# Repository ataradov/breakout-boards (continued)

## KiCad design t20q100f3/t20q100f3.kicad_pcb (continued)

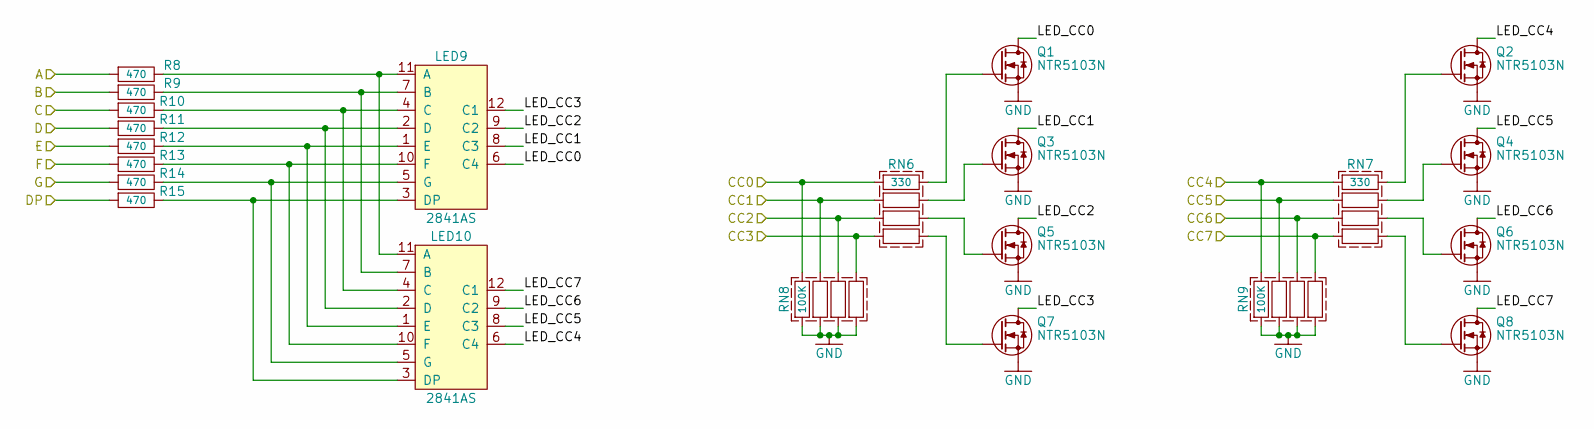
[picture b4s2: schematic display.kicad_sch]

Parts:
LED9, LED10: 2841AS
Q1, Q2, Q3, Q4, Q5, Q6, Q7, Q8: NTR5103N; SOT-23
R8, R9, R10, R11, R12, R13, R14, R15: 470; 0603
RN6, RN7: 330; 0603x4
RN8, RN9: 100K; 0603x4

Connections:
/Display/LED_CC0: LED9.6 (C4), Q1.3 (D)
/Display/LED_CC1: LED9.8 (C3), Q3.3 (D)
/Display/LED_CC2: LED9.9 (C2), Q5.3 (D)
/Display/LED_CC3: LED9.12 (C1), Q7.3 (D)
/Display/LED_CC4: LED10.6 (C4), Q2.3 (D)
/Display/LED_CC5: LED10.8 (C3), Q4.3 (D)
/Display/LED_CC6: LED10.9 (C2), Q6.3 (D)
/Display/LED_CC7: LED10.12 (C1), Q8.3 (D)
/LED_A: R8.1; also elsewhere on the board
/LED_B: R9.1; also elsewhere on the board
/LED_C: R10.1; also elsewhere on the board
/LED_CC0: RN6.1, RN8.8; also elsewhere on the board
/LED_CC1: RN6.2, RN8.7; also elsewhere on the board
/LED_CC2: RN6.3, RN8.6; also elsewhere on the board
/LED_CC3: RN6.4, RN8.5; also elsewhere on the board
/LED_CC4: RN7.1, RN9.8; also elsewhere on the board
/LED_CC5: RN7.2, RN9.7; also elsewhere on the board
/LED_CC6: RN7.3, RN9.6; also elsewhere on the board
/LED_CC7: RN7.4, RN9.5; also elsewhere on the board
/LED_D: R11.1; also elsewhere on the board
/LED_DP: R15.1; also elsewhere on the board
/LED_E: R12.1; also elsewhere on the board
/LED_F: R13.1; also elsewhere on the board
/LED_G: R14.1; also elsewhere on the board
GND: Q1.2 (S), Q2.2 (S), Q3.2 (S), Q4.2 (S), Q5.2 (S), Q6.2 (S), Q7.2 (S), Q8.2 (S), RN8.1, RN8.2, RN8.3, RN8.4, RN9.1, RN9.2, RN9.3, RN9.4; also elsewhere on the board
unnamed: LED9.11 (A), LED10.11 (A), R8.2
unnamed: LED9.7 (B), LED10.7 (B), R9.2
unnamed: LED9.4 (C), LED10.4 (C), R10.2
unnamed: LED9.2 (D), LED10.2 (D), R11.2
unnamed: LED9.3 (DP), LED10.3 (DP), R15.2
unnamed: LED9.1 (E), LED10.1 (E), R12.2
unnamed: LED9.10 (F), LED10.10 (F), R13.2
unnamed: LED9.5 (G), LED10.5 (G), R14.2
unnamed: Q1.1 (G), RN6.8
unnamed: Q2.1 (G), RN7.8
unnamed: Q3.1 (G), RN6.7
unnamed: Q4.1 (G), RN7.7
unnamed: Q5.1 (G), RN6.6
unnamed: Q6.1 (G), RN7.6
unnamed: Q7.1 (G), RN6.5
unnamed: Q8.1 (G), RN7.5

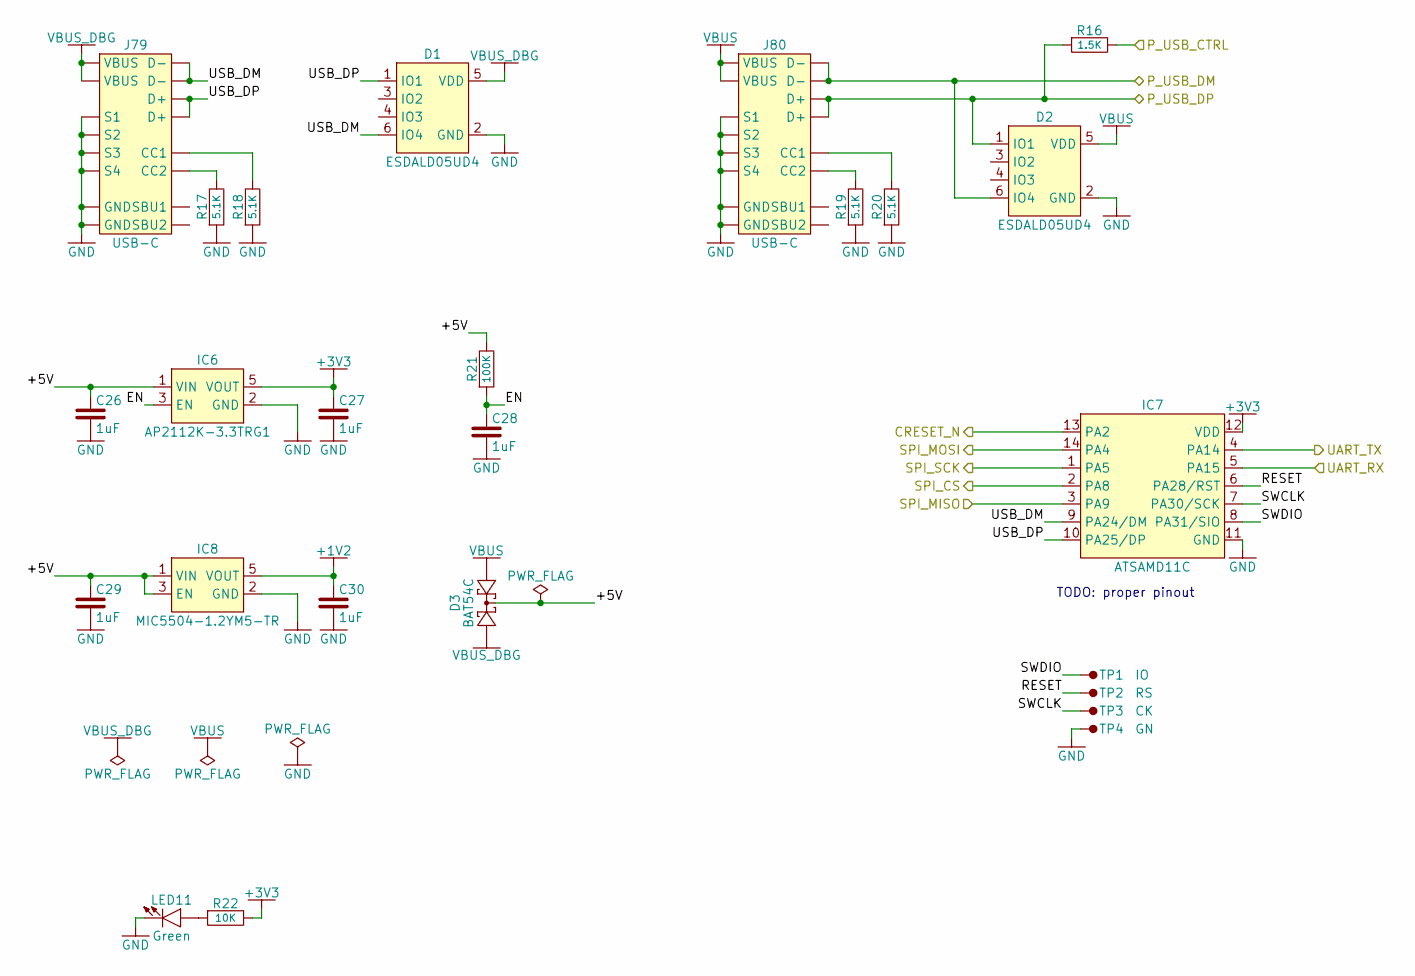
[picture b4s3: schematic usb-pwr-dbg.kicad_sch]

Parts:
C26, C27, C28, C29, C30: 1uF; 0603
D1, D2: ESDALD05UD4; SOT-23-6
D3: BAT54C; SOT-23
IC6: AP2112K-3.3TRG1; SOT-23-5
IC7: ATSAMD11C; SOIC-14
IC8: MIC5504-1.2YM5-TR; SOT-23-5
J79, J80: USB-C
LED11: Green; 0603_LED
R16: 1.5K; 0603
R17, R18, R19, R20: 5.1K; 0603
R21: 100K; 0603
R22: 10K; 0603
TP1: IO; TestPoint-1.27mm-SMD
TP2: RS; TestPoint-1.27mm-SMD
TP3: CK; TestPoint-1.27mm-SMD
TP4: GN; TestPoint-1.27mm-SMD

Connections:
+1V2: C30.2, IC8.5 (VOUT); also elsewhere on the board
+3V3: C27.2, IC6.5 (VOUT), IC7.12 (VDD), R22.2; also elsewhere on the board
/CRESET_N: IC7.13 (PA2); also elsewhere on the board
/P_USB_CTRL: R16.2; also elsewhere on the board
/P_USB_DM: D2.6 (IO4), J80.D-1 (D-), J80.D-2 (D-); also elsewhere on the board
/P_USB_DP: D2.1 (IO1), J80.D+1 (D+), J80.D+2 (D+), R16.1; also elsewhere on the board
/SPI_CS: IC7.2 (PA8); also elsewhere on the board
/SPI_MISO: IC7.3 (PA9); also elsewhere on the board
/SPI_MOSI: IC7.14 (PA4); also elsewhere on the board
/SPI_SCK: IC7.1 (PA5); also elsewhere on the board
/UART_RX: IC7.5 (PA15); also elsewhere on the board
/UART_TX: IC7.4 (PA14); also elsewhere on the board
/USB-Power-Debugger/+5V: C26.2, C29.2, D3.3, IC6.1 (VIN), IC8.1 (VIN), IC8.3 (EN), R21.2
/USB-Power-Debugger/EN: C28.2, IC6.3 (EN), R21.1
/USB-Power-Debugger/RESET: IC7.6 (PA28/RST), TP2.1
/USB-Power-Debugger/SWCLK: IC7.7 (PA30/SCK), TP3.1
/USB-Power-Debugger/SWDIO: IC7.8 (PA31/SIO), TP1.1
/USB-Power-Debugger/USB_DM: D1.6 (IO4), IC7.9 (PA24/DM), J79.D-1 (D-), J79.D-2 (D-)
/USB-Power-Debugger/USB_DP: D1.1 (IO1), IC7.10 (PA25/DP), J79.D+1 (D+), J79.D+2 (D+)
GND: C26.1, C27.1, C28.1, C29.1, C30.1, D1.2 (GND), D2.2 (GND), IC6.2 (GND), IC7.11 (GND), IC8.2 (GND), J79.GND1 (GND), J79.GND2 (GND), J79.S1, J79.S2, J79.S3, J79.S4, J80.GND1 (GND), J80.GND2 (GND), J80.S1, J80.S2, J80.S3, J80.S4, LED11.2 (K), R17.1, R18.1, R19.1, R20.1, TP4.1; also elsewhere on the board
unnamed: J79.CC1, R18.2
unnamed: J79.CC2, R17.2
unnamed: J80.CC1, R20.2
unnamed: J80.CC2, R19.2
unnamed: LED11.1 (A), R22.1
VBUS: D2.5 (VDD), D3.2, J80.VBUS1 (VBUS), J80.VBUS2 (VBUS)
VBUS_DBG: D1.5 (VDD), D3.1, J79.VBUS1 (VBUS), J79.VBUS2 (VBUS)

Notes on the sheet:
TODO: proper pinout

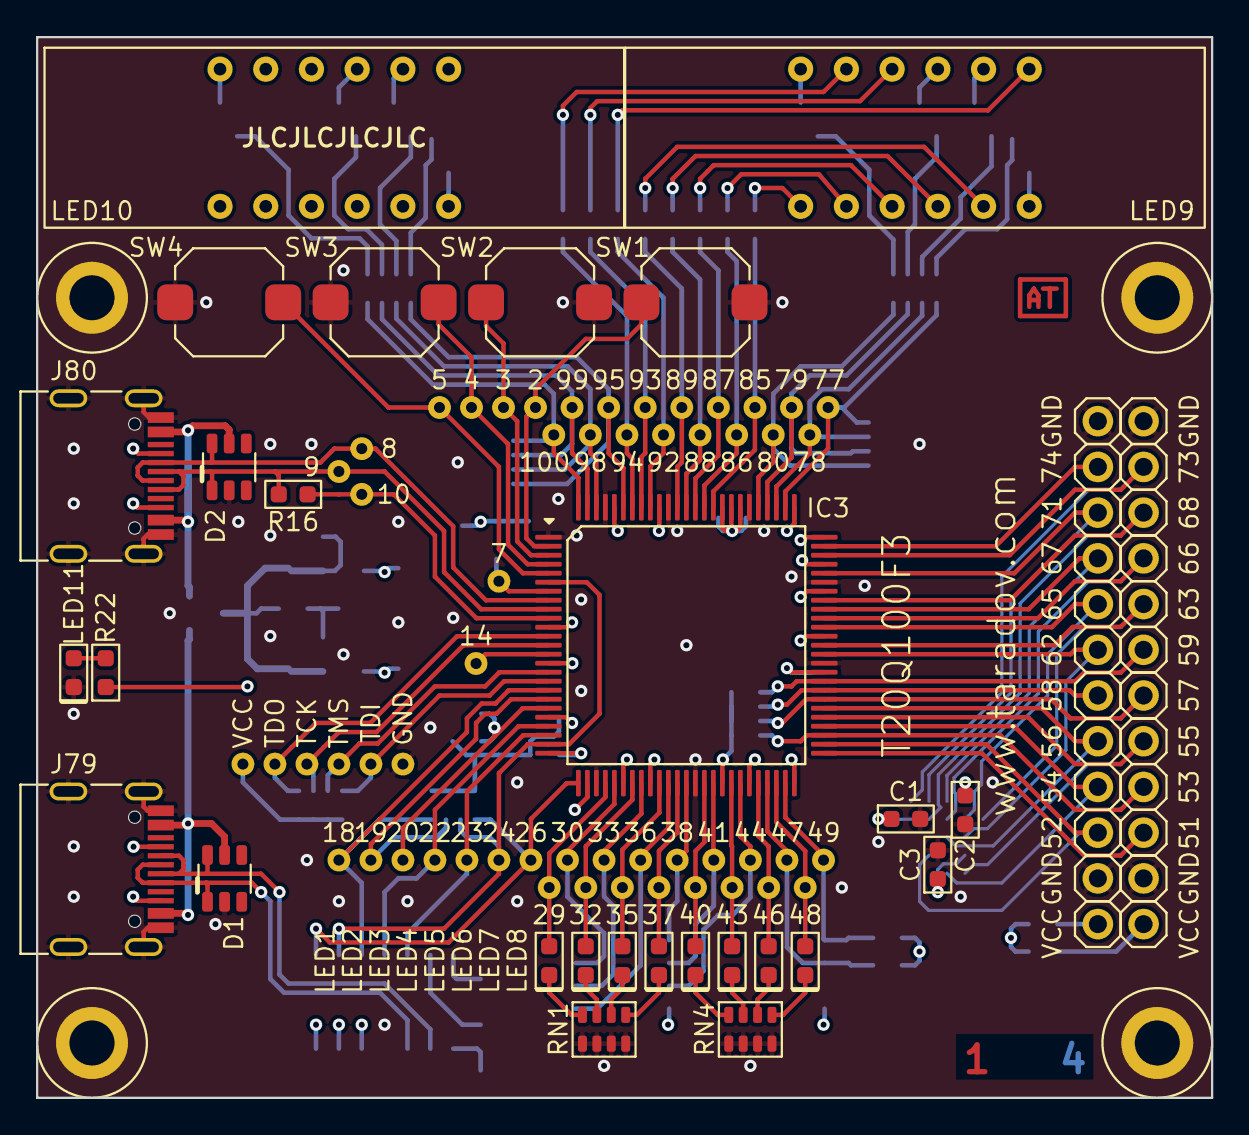
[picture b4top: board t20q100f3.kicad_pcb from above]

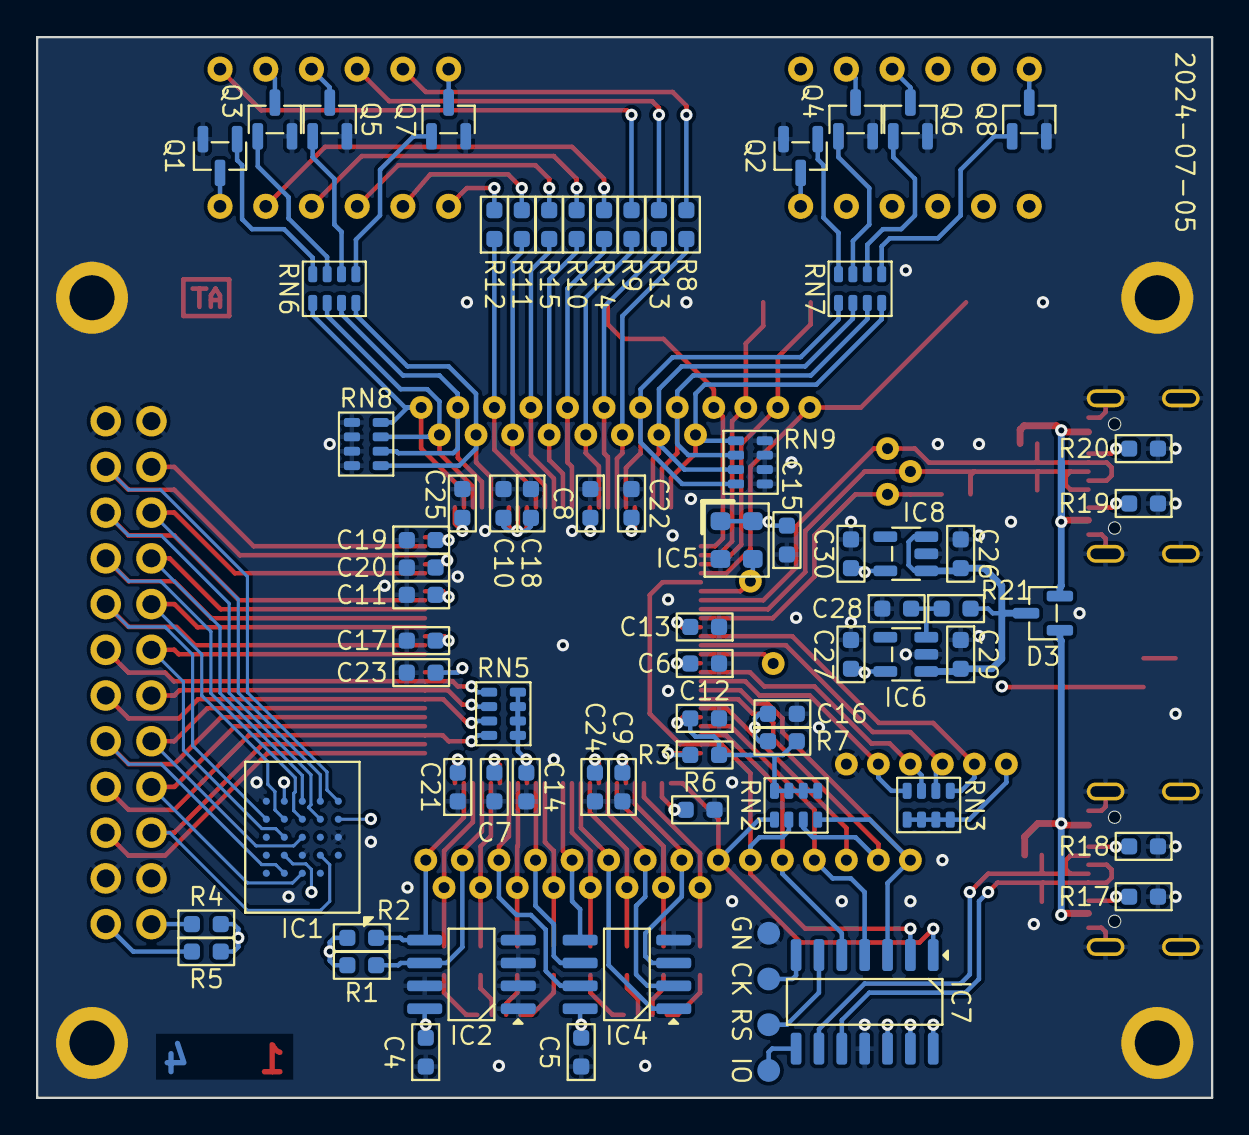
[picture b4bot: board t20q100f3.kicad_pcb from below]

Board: 4 copper layers, 65.3 x 58.9 mm, 184 parts (74 on the bottom side), 123 nets.

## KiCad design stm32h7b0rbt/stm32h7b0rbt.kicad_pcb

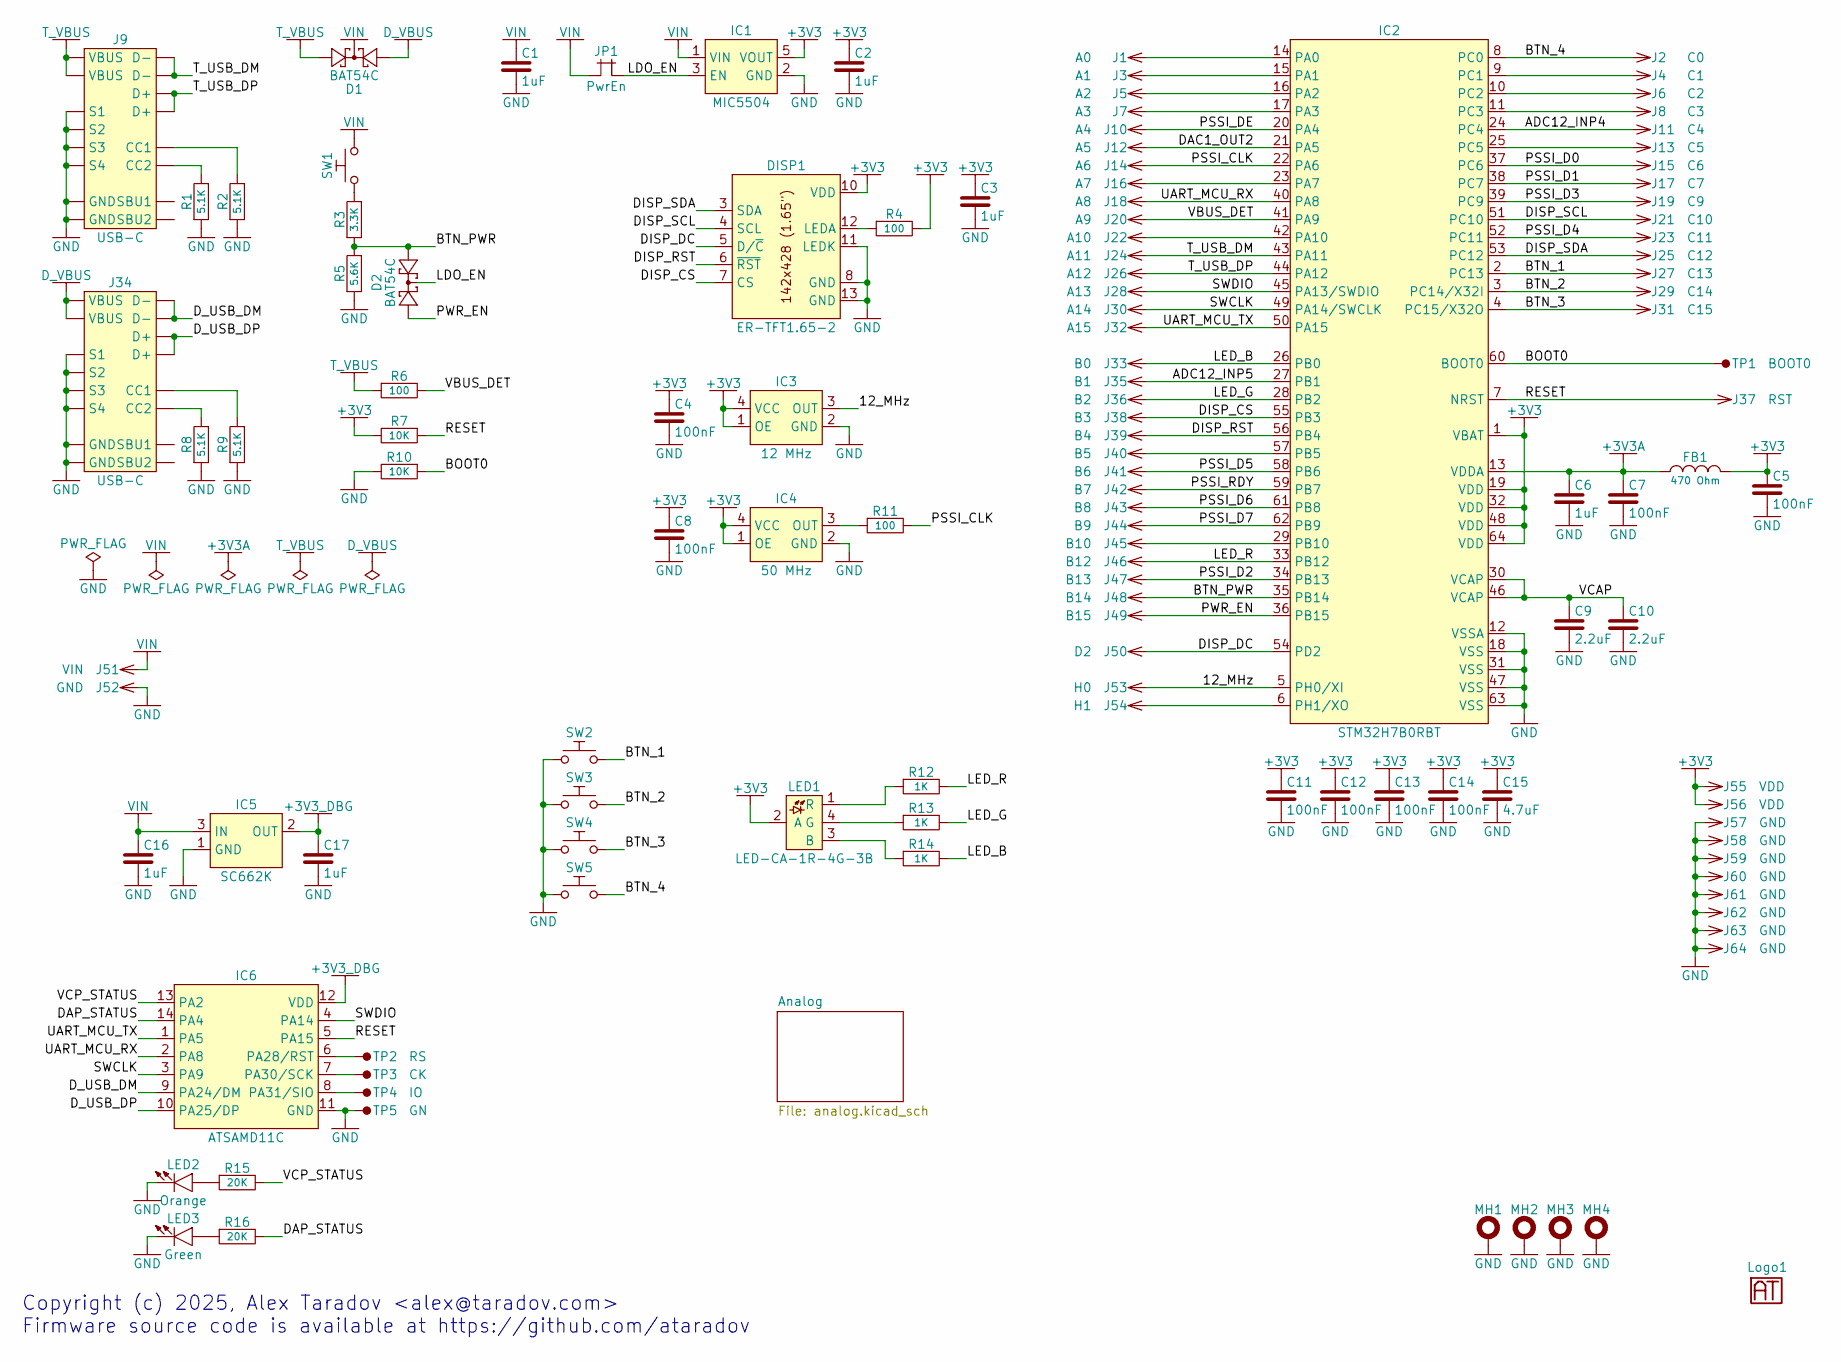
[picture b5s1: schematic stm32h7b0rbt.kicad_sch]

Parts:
C1, C2, C3, C6, C16, C17: 1uF; 0603
C4, C5, C7, C8, C11, C12, C13, C14: 100nF; 0603
C9, C10: 2.2uF; 0603
C15: 4.7uF; 0603
D1, D2: BAT54C; SOT-23
DISP1: ER-TFT1.65-2; ER-TFT1.65-2-TOP
FB1: 470 Ohm; 0603
IC1: MIC5504; SOT-23-5
IC2: STM32H7B0RBT; TQFP-64-0.5mm
IC3: 12 MHz; CDFN-4-3.2x2.5mm
IC4: 50 MHz; CDFN-4-3.2x2.5mm
IC5: SC662K; SOT-23
IC6: ATSAMD11C; SOIC-14
J1: A0; Pin-2.54mm
J2: C0; Pin-2.54mm
J3: A1; Pin-2.54mm
J4: C1; Pin-2.54mm
J5: A2; Pin-2.54mm
J6: C2; Pin-2.54mm
J7: A3; Pin-2.54mm
J8: C3; Pin-2.54mm
J9, J34: USB-C
J10: A4; Pin-2.54mm
J11: C4; Pin-2.54mm
J12: A5; Pin-2.54mm
J13: C5; Pin-2.54mm
J14: A6; Pin-2.54mm
J15: C6; Pin-2.54mm
J16: A7; Pin-2.54mm
J17: C7; Pin-2.54mm
J18: A8; Pin-2.54mm
J19: C9; Pin-2.54mm
J20: A9; Pin-2.54mm
J21: C10; Pin-2.54mm
J22: A10; Pin-2.54mm
J23: C11; Pin-2.54mm
J24: A11; Pin-2.54mm
J25: C12; Pin-2.54mm
J26: A12; Pin-2.54mm
J27: C13; Pin-2.54mm
J28: A13; Pin-2.54mm
J29: C14; Pin-2.54mm
J30: A14; Pin-2.54mm
J31: C15; Pin-2.54mm
J32: A15; Pin-2.54mm
J33: B0; Pin-2.54mm
J35: B1; Pin-2.54mm
J36: B2; Pin-2.54mm
J37: RST; Pin-2.54mm
J38: B3; Pin-2.54mm
J39: B4; Pin-2.54mm
J40: B5; Pin-2.54mm
J41: B6; Pin-2.54mm
J42: B7; Pin-2.54mm
J43: B8; Pin-2.54mm
J44: B9; Pin-2.54mm
J45: B10; Pin-2.54mm
J46: B12; Pin-2.54mm
J47: B13; Pin-2.54mm
J48: B14; Pin-2.54mm
J49: B15; Pin-2.54mm
J50: D2; Pin-2.54mm
J51: VIN; Pin-2.54mm
J52, J57, J58, J59, J60, J61, J62, J63, J64: GND; Pin-2.54mm
J53: H0; Pin-2.54mm
J54: H1; Pin-2.54mm
J55, J56: VDD; Pin-2.54mm
JP1: PwrEn; Jumper-2.54mm
LED1: LED-CA-1R-4G-3B; PLCC-4
LED2: Orange; 0603_LED
LED3: Green; 0603_LED
Logo1: Logo; Logo-Small
MH1, MH2, MH3, MH4: MH-2.5mm-4.0mm
R1, R2, R8, R9: 5.1K; 0603
R3: 3.3K; 0603
R4, R6, R11: 100; 0603
R5: 5.6K; 0603
R7, R10: 10K; 0603
R12, R13, R14: 1K; 0603
R15, R16: 20K; 0603
SW1, SW2, SW3, SW4, SW5: TactSwitch; TactSwitch-6mm-Sqare-SMD
TP1: BOOT0; TestPoint-1.27mm
TP2: RS; TestPoint-1.27mm-SMD
TP3: CK; TestPoint-1.27mm-SMD
TP4: IO; TestPoint-1.27mm-SMD
TP5: GN; TestPoint-1.27mm-SMD

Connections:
+3V3: C2.2, C3.2, C4.2, C5.2, C8.2, C11.2, C12.2, C13.2, C14.2, C15.2, DISP1.10 (VDD), FB1.2, IC1.5 (VOUT), IC2.1 (VBAT), IC2.19 (VDD), IC2.32 (VDD), IC2.48 (VDD), IC2.64 (VDD), IC3.1 (OE), IC3.4 (VCC), IC4.1 (OE), IC4.4 (VCC), J55.1, J56.1, LED1.2 (A), R4.2, R7.2
+3V3A: C6.2, C7.2, FB1.1, IC2.13 (VDDA); also elsewhere on the board
+3V3_DBG: C17.2, IC5.2 (OUT), IC6.12 (VDD)
/12_MHz: IC2.5 (PH0/XI), IC3.3 (OUT), J53.1
/ADC12_INP4: IC2.24 (PC4), J11.1
/ADC12_INP5: IC2.27 (PB1), J35.1
/BOOT0: IC2.60 (BOOT0), R10.1, TP1.1
/BTN_1: IC2.2 (PC13), J27.1, SW2.2
/BTN_2: IC2.3 (PC14/X32I), J29.1, SW3.2
/BTN_3: IC2.4 (PC15/X32O), J31.1, SW4.2
/BTN_4: IC2.8 (PC0), J2.1, SW5.2
/BTN_PWR: D2.2, IC2.35 (PB14), J48.1, R3.1, R5.2
/DAC1_OUT2: IC2.21 (PA5), J12.1
/DAP_STATUS: IC6.14 (PA4), R16.2
/DISP_CS: DISP1.7 (CS), IC2.55 (PB3), J38.1
/DISP_DC: DISP1.5 (D/~C), IC2.54 (PD2), J50.1
/DISP_RST: DISP1.6 (~RST), IC2.56 (PB4), J39.1
/DISP_SCL: DISP1.4 (SCL), IC2.51 (PC10), J21.1
/DISP_SDA: DISP1.3 (SDA), IC2.53 (PC12), J25.1
/D_USB_DM: IC6.9 (PA24/DM), J34.D-1 (D-), J34.D-2 (D-)
/D_USB_DP: IC6.10 (PA25/DP), J34.D+1 (D+), J34.D+2 (D+)
/LDO_EN: D2.3, IC1.3 (EN), JP1.2
/LED_B: IC2.26 (PB0), J33.1, R14.2
/LED_G: IC2.28 (PB2), J36.1, R13.2
/LED_R: IC2.33 (PB12), J46.1, R12.2
/PSSI_CLK: IC2.22 (PA6), J14.1, R11.2
/PSSI_D0: IC2.37 (PC6), J15.1
/PSSI_D1: IC2.38 (PC7), J17.1
/PSSI_D2: IC2.34 (PB13), J47.1
/PSSI_D3: IC2.39 (PC9), J19.1
/PSSI_D4: IC2.52 (PC11), J23.1
/PSSI_D5: IC2.58 (PB6), J41.1
/PSSI_D6: IC2.61 (PB8), J43.1
/PSSI_D7: IC2.62 (PB9), J44.1
/PSSI_DE: IC2.20 (PA4), J10.1
/PSSI_RDY: IC2.59 (PB7), J42.1
/PWR_EN: D2.1, IC2.36 (PB15), J49.1
/RESET: IC2.7 (NRST), IC6.5 (PA15), J37.1, R7.1
/SWCLK: IC2.49 (PA14/SWCLK), IC6.3 (PA9), J30.1
/SWDIO: IC2.45 (PA13/SWDIO), IC6.4 (PA14), J28.1
/T_USB_DM: IC2.43 (PA11), J9.D-1 (D-), J9.D-2 (D-), J24.1
/T_USB_DP: IC2.44 (PA12), J9.D+1 (D+), J9.D+2 (D+), J26.1
/UART_MCU_RX: IC2.40 (PA8), IC6.2 (PA8), J18.1
/UART_MCU_TX: IC2.50 (PA15), IC6.1 (PA5), J32.1
/VBUS_DET: IC2.41 (PA9), J20.1, R6.2
/VCAP: C9.2, C10.2, IC2.30 (VCAP), IC2.46 (VCAP)
/VCP_STATUS: IC6.13 (PA2), R15.2
D_VBUS: D1.1, J34.VBUS1 (VBUS), J34.VBUS2 (VBUS)
GND: C1.1, C2.1, C3.1, C4.1, C5.1, C6.1, C7.1, C8.1, C9.1, C10.1, C11.1, C12.1, C13.1, C14.1, C15.1, C16.1, C17.1, DISP1.8 (GND), DISP1.11 (LEDK), DISP1.13 (GND), IC1.2 (GND), IC2.12 (VSSA), IC2.18 (VSS), IC2.31 (VSS), IC2.47 (VSS), IC2.63 (VSS), IC3.2 (GND), IC4.2 (GND), IC5.1 (GND), IC6.11 (GND), J9.GND1 (GND), J9.GND2 (GND), J9.S1, J9.S2, J9.S3, J9.S4, J34.GND1 (GND), J34.GND2 (GND), J34.S1, J34.S2, J34.S3, J34.S4, J52.1, J57.1, J58.1, J59.1, J60.1, J61.1, J62.1, J63.1, J64.1, LED2.2 (K), LED3.2 (K), MH1.1, MH2.1, MH3.1, MH4.1, R1.1, R2.1, R5.1, R8.1, R9.1, R10.2, SW2.1, SW3.1, SW4.1, SW5.1, TP5.1; also elsewhere on the board
unnamed: DISP1.12 (LEDA), R4.1
unnamed: IC2.14 (PA0), J1.1
unnamed: IC2.15 (PA1), J3.1
unnamed: IC2.16 (PA2), J5.1
unnamed: IC2.17 (PA3), J7.1
unnamed: IC2.23 (PA7), J16.1
unnamed: IC2.42 (PA10), J22.1
unnamed: IC2.57 (PB5), J40.1
unnamed: IC2.29 (PB10), J45.1
unnamed: IC2.9 (PC1), J4.1
unnamed: IC2.10 (PC2), J6.1
unnamed: IC2.11 (PC3), J8.1
unnamed: IC2.25 (PC5), J13.1
unnamed: IC2.6 (PH1/XO), J54.1
unnamed: IC4.3 (OUT), R11.1
unnamed: IC6.6 (PA28/RST), TP2.1
unnamed: IC6.7 (PA30/SCK), TP3.1
unnamed: IC6.8 (PA31/SIO), TP4.1
unnamed: J9.CC1, R2.2
unnamed: J9.CC2, R1.2
unnamed: J34.CC1, R9.2
unnamed: J34.CC2, R8.2
unnamed: LED1.3 (B), R14.1
unnamed: LED1.4 (G), R13.1
unnamed: LED1.1 (R), R12.1
unnamed: LED2.1 (A), R15.1
unnamed: LED3.1 (A), R16.1
unnamed: R3.2, SW1.1
T_VBUS: D1.2, J9.VBUS1 (VBUS), J9.VBUS2 (VBUS), R6.1
VIN: C1.2, C16.2, D1.3, IC1.1 (VIN), IC5.3 (IN), J51.1, JP1.1, SW1.2

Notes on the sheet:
Copyright (c) 2025, Alex Taradov <alex@taradov.com> Firmware source code is available at https://github.com/ataradov

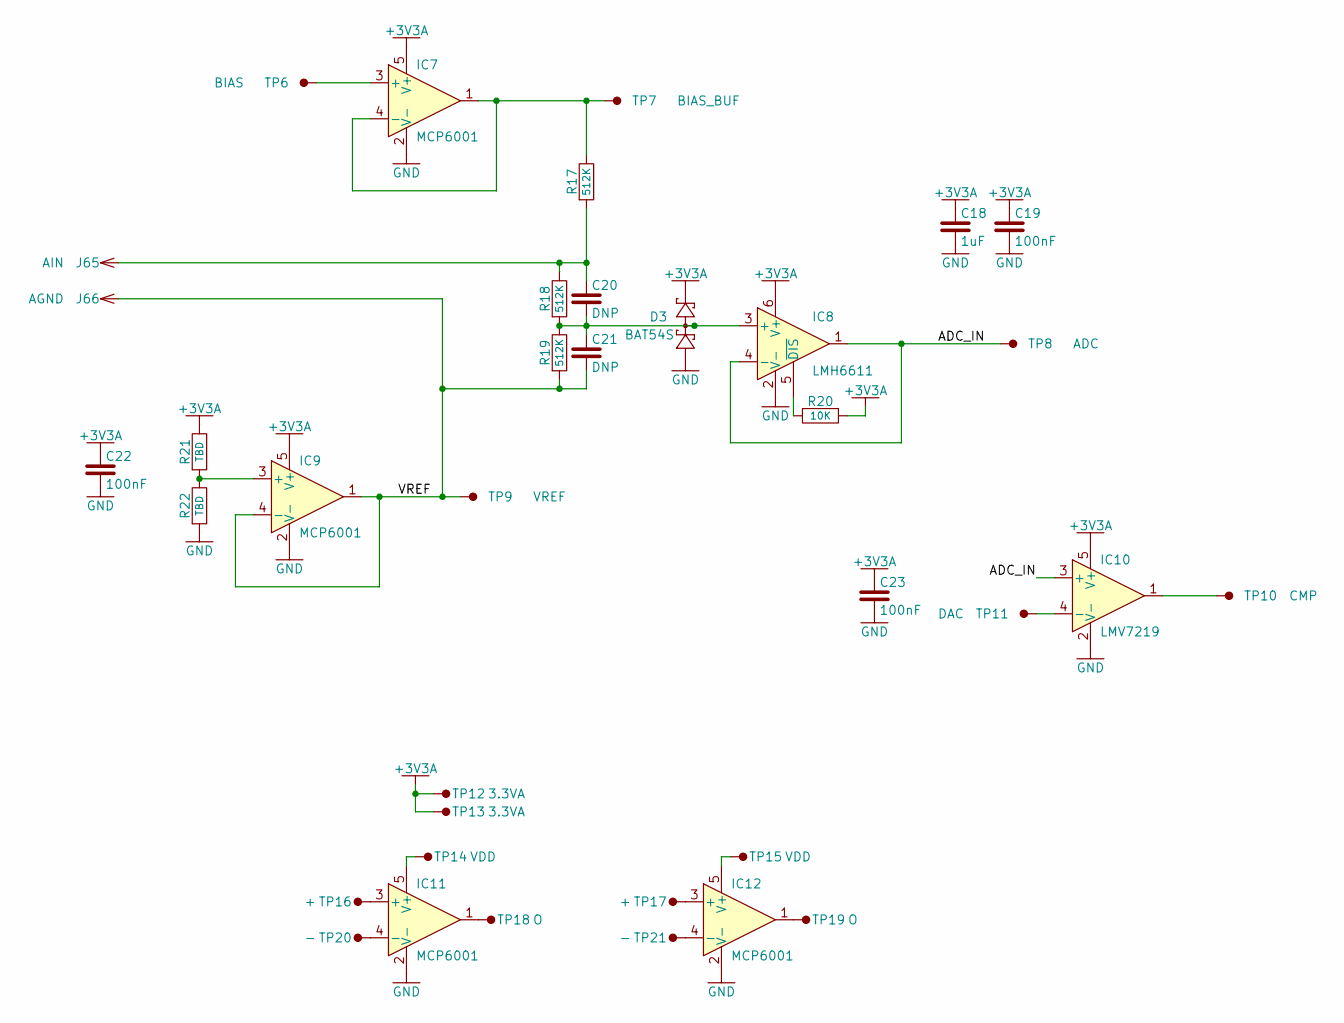
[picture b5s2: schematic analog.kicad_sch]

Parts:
C18: 1uF; 0603
C19, C22, C23: 100nF; 0603
C20, C21: DNP; 0603
D3: BAT54S; SOT-23
IC7, IC9, IC11, IC12: MCP6001; SOT-23-5
IC8: LMH6611; SOT-23-6
IC10: LMV7219; SOT-23-5
J65: AIN; Pin-2.54mm
J66: AGND; Pin-2.54mm
R17, R18, R19: 512K; 0603
R20: 10K; 0603
R21, R22: TBD; 0603
TP6: BIAS; TestPoint-1.27mm
TP7: BIAS_BUF; TestPoint-1.27mm
TP8: ADC; TestPoint-1.27mm
TP9: VREF; TestPoint-1.27mm
TP10: CMP; TestPoint-1.27mm
TP11: DAC; TestPoint-1.27mm
TP12, TP13: 3.3VA; TestPoint-1.27mm
TP14, TP15: VDD; TestPoint-1.27mm
TP16, TP17: +; TestPoint-1.27mm
TP18, TP19: O; TestPoint-1.27mm
TP20, TP21: -; TestPoint-1.27mm

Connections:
+3V3A: C18.2, C19.2, C22.2, C23.2, D3.2, IC7.5 (V+), IC8.6 (V+), IC9.5 (V+), IC10.5 (V+), R20.2, R21.2, TP12.1, TP13.1; also elsewhere on the board
/Analog/ADC_IN: IC8.1, IC8.4 (-), IC10.3 (+), TP8.1
/Analog/VREF: C21.1, IC9.1, IC9.4 (-), J66.1, R19.1, TP9.1
GND: C18.1, C19.1, C22.1, C23.1, D3.1, IC7.2 (V-), IC8.2 (V-), IC9.2 (V-), IC10.2 (V-), IC11.2 (V-), IC12.2 (V-), R22.1; also elsewhere on the board
unnamed: C20.2, J65.1, R17.1, R18.2
unnamed: IC7.3 (+), TP6.1
unnamed: IC7.1, IC7.4 (-), R17.2, TP7.1
unnamed: C20.1, C21.2, D3.3, IC8.3 (+), R18.1, R19.2
unnamed: IC8.5 (~DIS), R20.1
unnamed: IC9.3 (+), R21.1, R22.2
unnamed: IC10.4 (-), TP11.1
unnamed: IC10.1, TP10.1
unnamed: IC11.3 (+), TP16.1
unnamed: IC11.4 (-), TP20.1
unnamed: IC11.1, TP18.1
unnamed: IC11.5 (V+), TP14.1
unnamed: IC12.3 (+), TP17.1
unnamed: IC12.4 (-), TP21.1
unnamed: IC12.1, TP19.1
unnamed: IC12.5 (V+), TP15.1

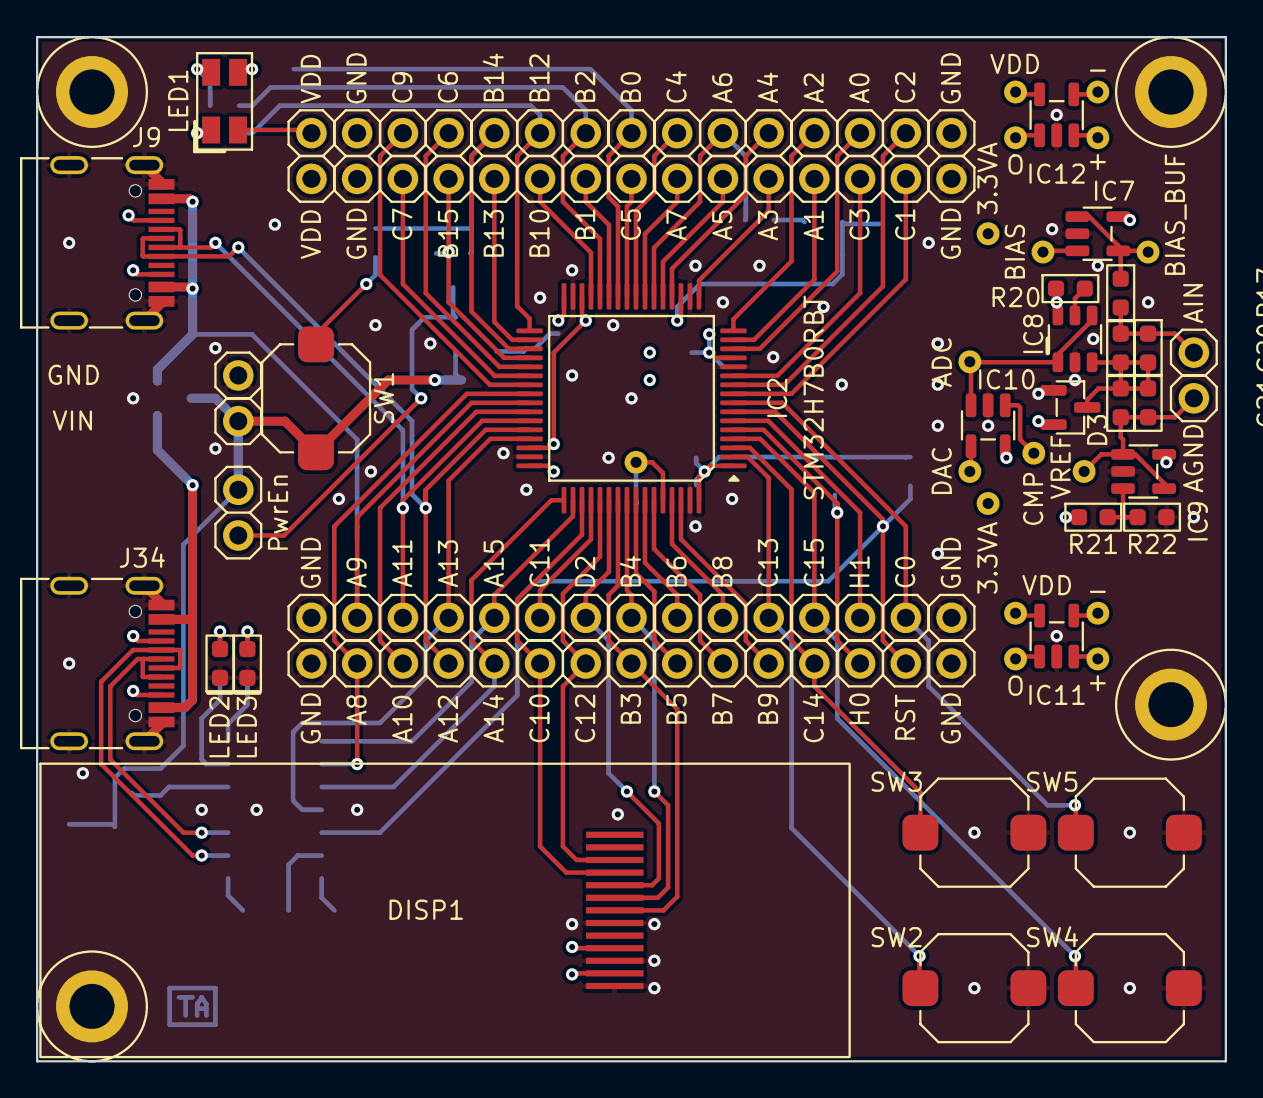
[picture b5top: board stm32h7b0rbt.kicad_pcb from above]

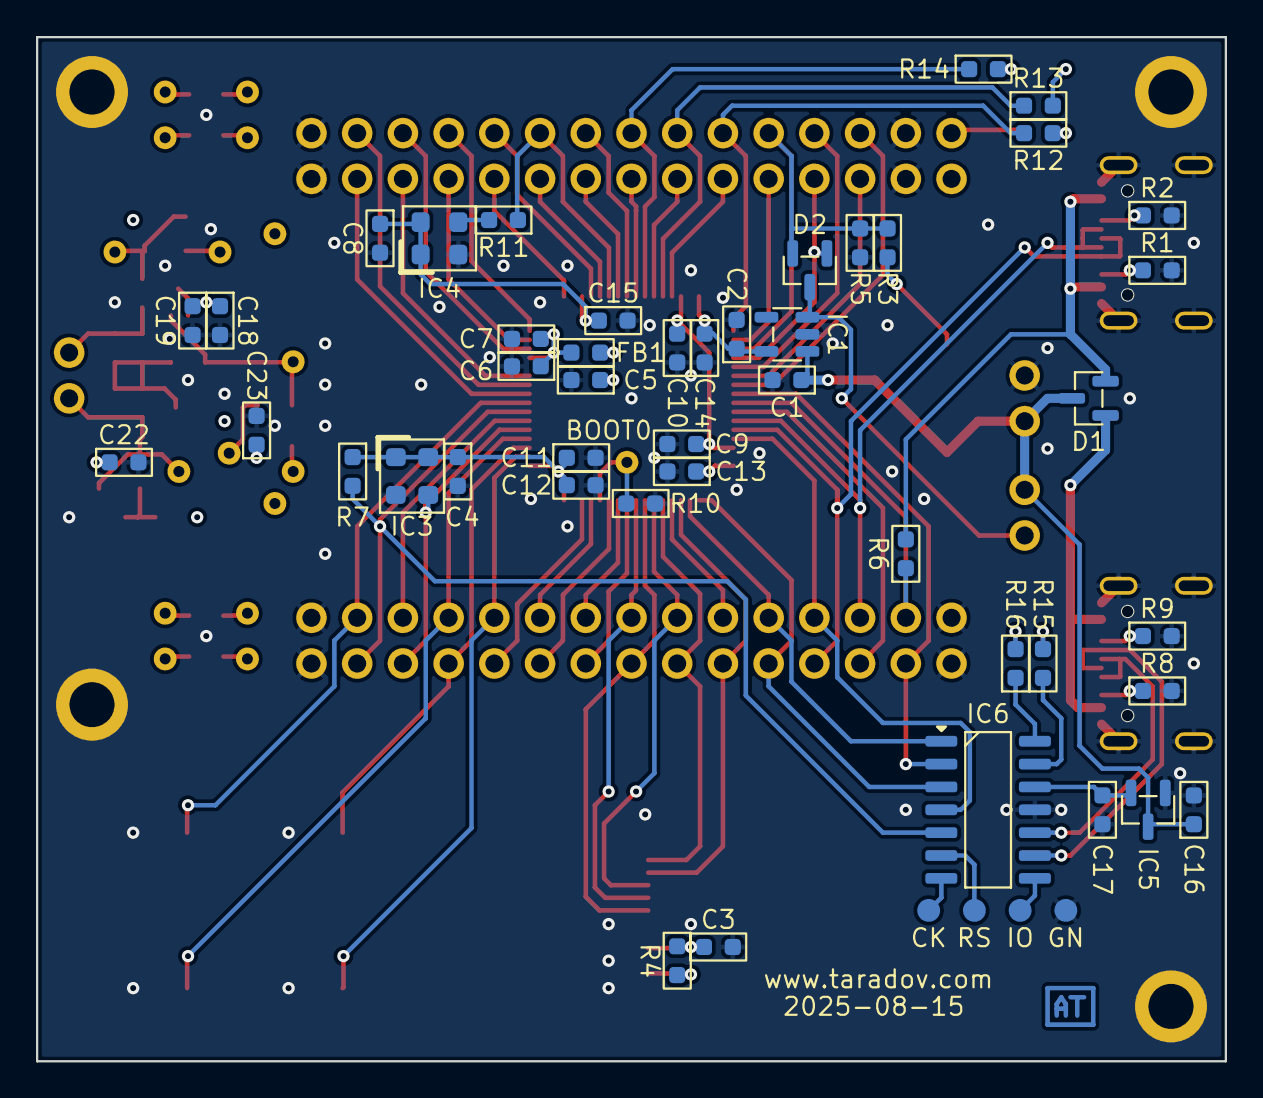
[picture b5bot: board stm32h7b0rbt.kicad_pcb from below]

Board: 4 copper layers, 66.0 x 56.9 mm, 163 parts (51 on the bottom side), 97 nets.

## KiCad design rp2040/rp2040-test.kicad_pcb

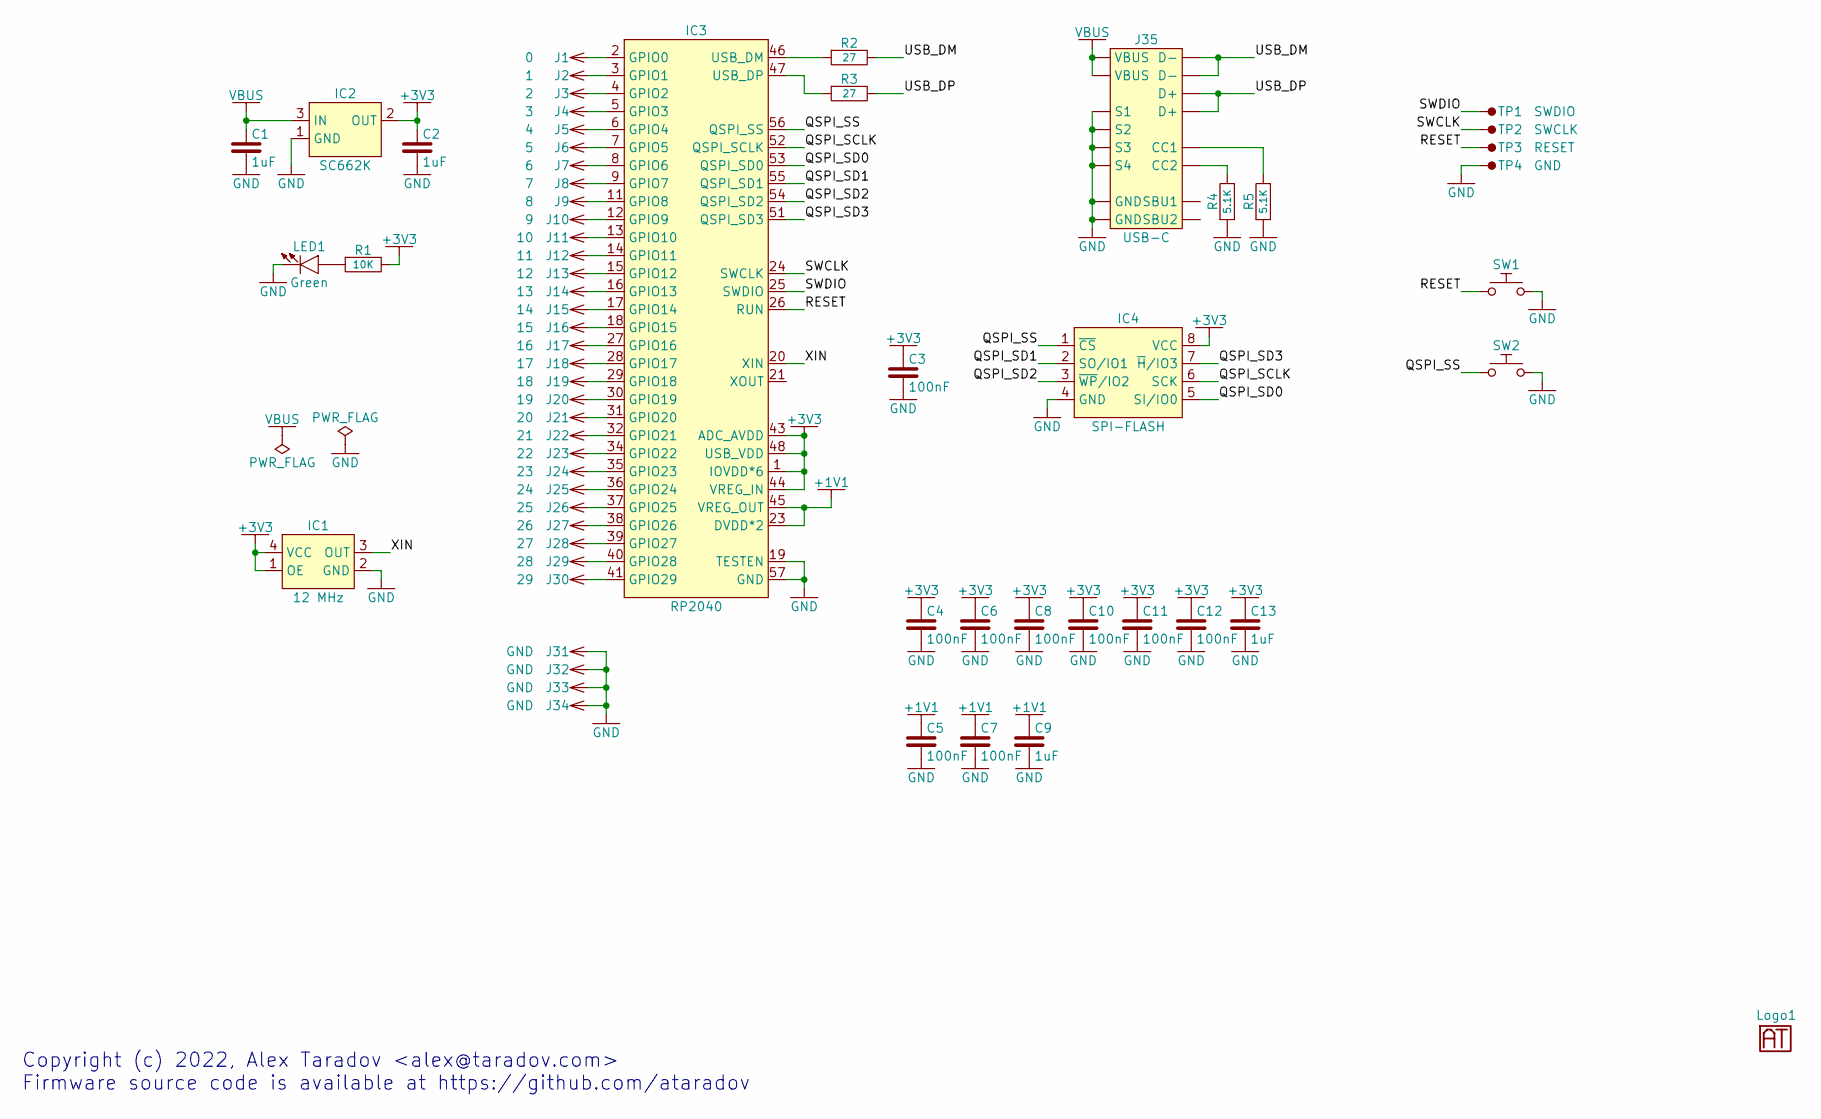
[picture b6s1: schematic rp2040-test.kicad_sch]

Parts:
C1, C2: 1uF; 0603
C3, C4, C5, C6, C7, C8, C10, C11, C12: 100nF; 0402
C9, C13: 1uF; 0402
IC1: 12 MHz; CDFN-4-3.2x2.5mm
IC2: SC662K; SOT-23
IC3: RP2040; QFN-56-0.4mm
IC4: SPI-FLASH; USON-8-3x2mm
J1: 0; Pin-2.54mm
J2: 1; Pin-2.54mm
J3: 2; Pin-2.54mm
J4: 3; Pin-2.54mm
J5: 4; Pin-2.54mm
J6: 5; Pin-2.54mm
J7: 6; Pin-2.54mm
J8: 7; Pin-2.54mm
J9: 8; Pin-2.54mm
J10: 9; Pin-2.54mm
J11: 10; Pin-2.54mm
J12: 11; Pin-2.54mm
J13: 12; Pin-2.54mm
J14: 13; Pin-2.54mm
J15: 14; Pin-2.54mm
J16: 15; Pin-2.54mm
J17: 16; Pin-2.54mm
J18: 17; Pin-2.54mm
J19: 18; Pin-2.54mm
J20: 19; Pin-2.54mm
J21: 20; Pin-2.54mm
J22: 21; Pin-2.54mm
J23: 22; Pin-2.54mm
J24: 23; Pin-2.54mm
J25: 24; Pin-2.54mm
J26: 25; Pin-2.54mm
J27: 26; Pin-2.54mm
J28: 27; Pin-2.54mm
J29: 28; Pin-2.54mm
J30: 29; Pin-2.54mm
J31, J32, J33, J34: GND; Pin-2.54mm
J35: USB-C
LED1: Green; 0603
Logo1: Logo
R1: 10K; 0603
R2, R3: 27; 0603
R4, R5: 5.1K; 0603
SW1, SW2: TactSwitch; TactSwitch-6mm-Sqare-SMD
TP1: SWDIO; TestPoint-1.27mm-SMD
TP2: SWCLK; TestPoint-1.27mm-SMD
TP3: RESET; TestPoint-1.27mm-SMD
TP4: GND; TestPoint-1.27mm-SMD

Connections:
+1V1: C5.2, C7.2, C9.2, IC3.23 (DVDD*2), IC3.45 (VREG_OUT), IC3.50 (DVDD*2)
+3V3: C2.2, C3.2, C4.2, C6.2, C8.2, C10.2, C11.2, C12.2, C13.2, IC1.1 (OE), IC1.4 (VCC), IC2.2 (OUT), IC3.1 (IOVDD*6), IC3.10 (IOVDD*6), IC3.22 (IOVDD*6), IC3.33 (IOVDD*6), IC3.42 (IOVDD*6), IC3.43 (ADC_AVDD), IC3.44 (VREG_IN), IC3.48 (USB_VDD), IC3.49 (IOVDD*6), IC4.8 (VCC), R1.2
/QSPI_SCLK: IC3.52 (QSPI_SCLK), IC4.6 (SCK)
/QSPI_SD0: IC3.53 (QSPI_SD0), IC4.5 (SI/IO0)
/QSPI_SD1: IC3.55 (QSPI_SD1), IC4.2 (SO/IO1)
/QSPI_SD2: IC3.54 (QSPI_SD2), IC4.3 (~WP/IO2)
/QSPI_SD3: IC3.51 (QSPI_SD3), IC4.7 (~H/IO3)
/QSPI_SS: IC3.56 (QSPI_SS), IC4.1 (~CS), SW2.1
/RESET: IC3.26 (RUN), SW1.1, TP3.1
/SWCLK: IC3.24 (SWCLK), TP2.1
/SWDIO: IC3.25 (SWDIO), TP1.1
/USB_DM: J35.D-1 (D-), J35.D-2 (D-), R2.2
/USB_DP: J35.D+1 (D+), J35.D+2 (D+), R3.2
/XIN: IC1.3 (OUT), IC3.20 (XIN)
GND: C1.1, C2.1, C3.1, C4.1, C5.1, C6.1, C7.1, C8.1, C9.1, C10.1, C11.1, C12.1, C13.1, IC1.2 (GND), IC2.1 (GND), IC3.19 (TESTEN), IC3.57 (GND), IC4.4 (GND), J31.1, J32.1, J33.1, J34.1, J35.GND1 (GND), J35.GND2 (GND), J35.S1, J35.S2, J35.S3, J35.S4, LED1.2 (K), R4.1, R5.1, SW1.2, SW2.2, TP4.1
unnamed: IC3.2 (GPIO0), J1.1
unnamed: IC3.3 (GPIO1), J2.1
unnamed: IC3.4 (GPIO2), J3.1
unnamed: IC3.5 (GPIO3), J4.1
unnamed: IC3.6 (GPIO4), J5.1
unnamed: IC3.7 (GPIO5), J6.1
unnamed: IC3.8 (GPIO6), J7.1
unnamed: IC3.9 (GPIO7), J8.1
unnamed: IC3.11 (GPIO8), J9.1
unnamed: IC3.12 (GPIO9), J10.1
unnamed: IC3.13 (GPIO10), J11.1
unnamed: IC3.14 (GPIO11), J12.1
unnamed: IC3.15 (GPIO12), J13.1
unnamed: IC3.16 (GPIO13), J14.1
unnamed: IC3.17 (GPIO14), J15.1
unnamed: IC3.18 (GPIO15), J16.1
unnamed: IC3.27 (GPIO16), J17.1
unnamed: IC3.28 (GPIO17), J18.1
unnamed: IC3.29 (GPIO18), J19.1
unnamed: IC3.30 (GPIO19), J20.1
unnamed: IC3.31 (GPIO20), J21.1
unnamed: IC3.32 (GPIO21), J22.1
unnamed: IC3.34 (GPIO22), J23.1
unnamed: IC3.35 (GPIO23), J24.1
unnamed: IC3.36 (GPIO24), J25.1
unnamed: IC3.37 (GPIO25), J26.1
unnamed: IC3.38 (GPIO26), J27.1
unnamed: IC3.39 (GPIO27), J28.1
unnamed: IC3.40 (GPIO28), J29.1
unnamed: IC3.41 (GPIO29), J30.1
unnamed: IC3.46 (USB_DM), R2.1
unnamed: IC3.47 (USB_DP), R3.1
unnamed: J35.CC1, R5.2
unnamed: J35.CC2, R4.2
unnamed: LED1.1 (A), R1.1
VBUS: C1.2, IC2.3 (IN), J35.VBUS1 (VBUS), J35.VBUS2 (VBUS)

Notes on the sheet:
Copyright (c) 2022, Alex Taradov <alex@taradov.com> Firmware source code is available at https://github.com/ataradov
